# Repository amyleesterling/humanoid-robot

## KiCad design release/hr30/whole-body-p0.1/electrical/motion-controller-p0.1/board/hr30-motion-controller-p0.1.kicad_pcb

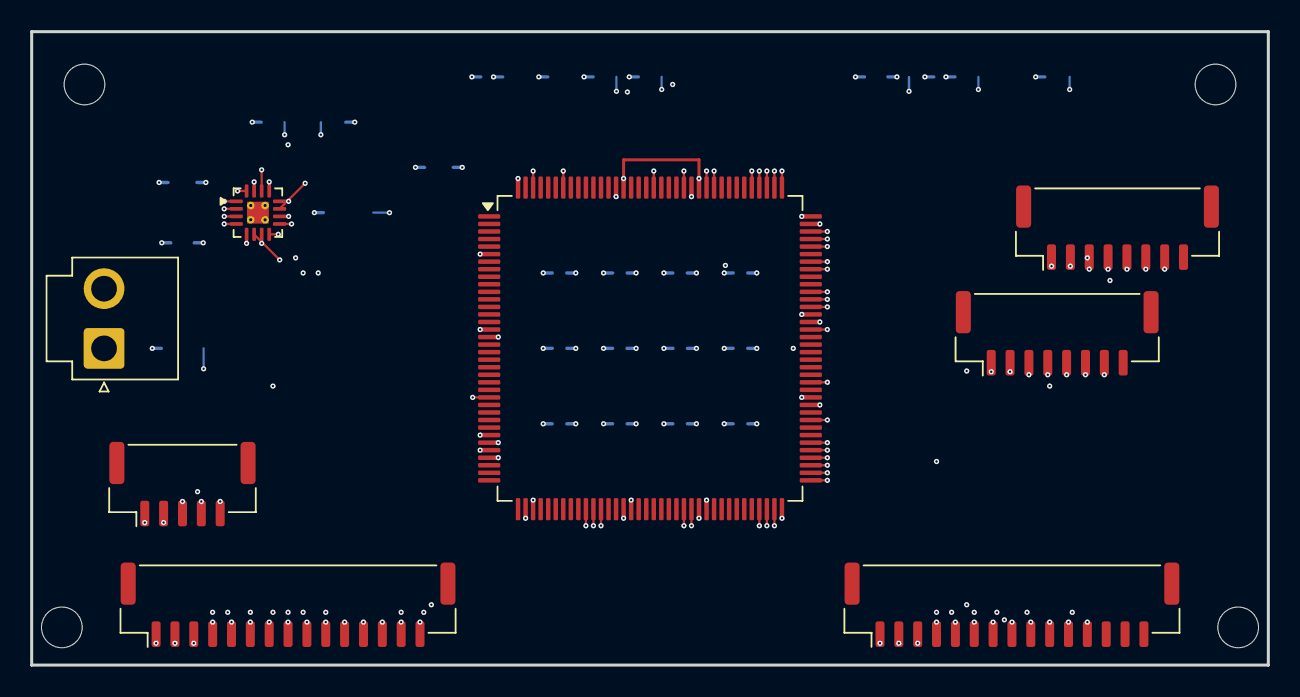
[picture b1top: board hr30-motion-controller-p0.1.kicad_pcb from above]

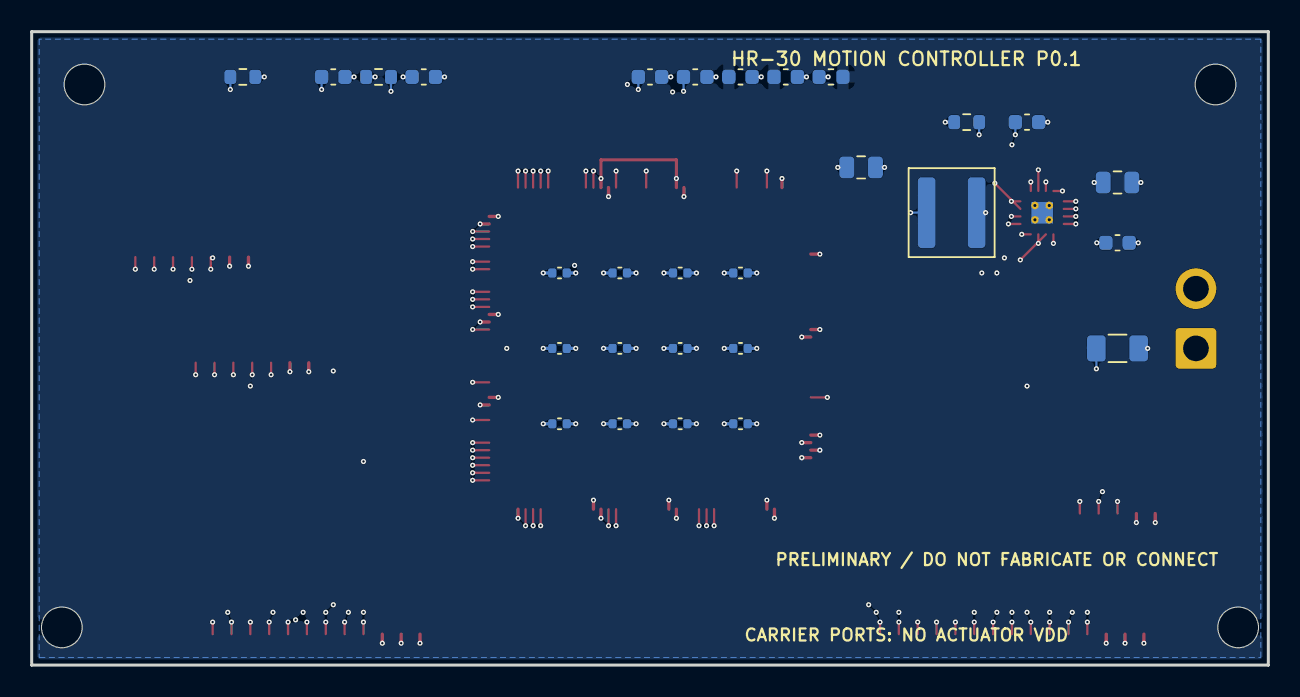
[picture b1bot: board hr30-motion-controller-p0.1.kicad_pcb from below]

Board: 6 copper layers, 82.0 x 42.0 mm, 40 parts (28 on the bottom side), 45 nets.

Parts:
C1, C2, C3, C4, C5, C6, C7, C8, C9, C10, C11, C12: 100 nF MCU supply bypass; C_0402_1005Metric
CANA1: 1 uF analog bypass; C_0603_1608Metric
CANA2: 100 nF analog bypass; C_0603_1608Metric
CBULK1: 4.7 uF MCU bulk; C_0603_1608Metric
CIN1: 10 uF 10 V X7R input; C_0805_2012Metric
CIN2: 100 nF 50 V X7R AVIN; C_0603_1608Metric
CNRST: 100 nF NRST filter; C_0603_1608Metric
COUT1: 22 uF 6.3 V X5R output; C_0805_2012Metric
CSS1: 3.3 nF soft-start; C_0603_1608Metric
CVC1: 2.2 uF VCAP1; C_0603_1608Metric
CVC2: 2.2 uF VCAP2; C_0603_1608Metric
F1: resettable input protection - selection required; Fuse_1206_3216Metric
FB1: analog-rail ferrite; L_0603_1608Metric
J1: Protected auxiliary 5 V input; JST_VH_B2P-VH-B_1x02_P3.96mm_Vertical
JACT1: structured action SPI boundary; JST_GH_BM08B-GHS-TBT_1x08-1MP_P1.25mm_Vertical
JCA1: Carrier A logic-only interface; JST_GH_BM15B-GHS-TBT_1x15-1MP_P1.25mm_Vertical
JCB1: Carrier B logic-only interface; JST_GH_BM15B-GHS-TBT_1x15-1MP_P1.25mm_Vertical
JDBG1: SWD programming/debug; JST_GH_BM05B-GHS-TBT_1x05-1MP_P1.25mm_Vertical
JIO1: deterministic status / inhibit I/O; JST_GH_BM08B-GHS-TBT_1x08-1MP_P1.25mm_Vertical
L1: 2.2 uH power inductor; L_Coilcraft_XAL5030-XXX
MHM1, MHM2, MHM3, MHM4: M2.5 BOARD-ONLY; TRAY STACK VALIDATION OPEN; MountingHole_2.7mm_M2.5
RBOOT: 100 k BOOT0 pull-down; R_0603_1608Metric
RNRST: 10 k NRST pull-up; R_0603_1608Metric
RPG1: 100 k power-good pull-up; R_0603_1608Metric
U1: STM32H743ZIT6 deterministic motion controller; LQFP-144_20x20mm_P0.5mm
U2: TPS62132 3.3 V / 3 A buck; VQFN-16-1EP_3x3mm_P0.5mm_EP1.45x1.45mm_ThermalVias

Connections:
ACTION_READY: JACT1.7, U1.126
ACTION_SPI_CS: JACT1.3, U1.73
ACTION_SPI_MISO: JACT1.5, U1.75
ACTION_SPI_MOSI: JACT1.6, U1.76
ACTION_SPI_SCK: JACT1.4, U1.74
AUX_5V_SAFE: F1.1, J1.2
BUCK_PG: RPG1.2, U2.4
BUCK_SS: CSS1.1, U2.9
BUCK_SW: L1.1, U2.1, U2.2, U2.3
CTRL_3V3: C1.1, C2.1, C3.1, C4.1, C5.1, C6.1, C7.1, C8.1, C9.1, C10.1, C11.1, C12.1, CBULK1.1, COUT1.1, FB1.1, JACT1.2, JCA1.3, JCB1.3, JDBG1.2, JIO1.2, L1.2, RNRST.1, RPG1.1, U1.6, U1.17, U1.30, U1.39, U1.52, U1.62, U1.72, U1.84, U1.95, U1.108, U1.121, U1.131, U1.144, U2.14
CTRL_3V3_ANALOG: CANA1.1, CANA2.1, FB1.2, U1.32, U1.33
CTRL_5V: CIN1.1, CIN2.1, F1.2, JCA1.2, JCB1.2, U2.10, U2.11, U2.12, U2.13
CTRL_GND: C1.2, C2.2, C3.2, C4.2, C5.2, C6.2, C7.2, C8.2, C9.2, C10.2, C11.2, C12.2, CANA1.2, CANA2.2, CBULK1.2, CIN1.2, CIN2.2, CNRST.2, COUT1.2, CSS1.2, CVC1.2, CVC2.2, J1.1, JACT1.1, JCA1.1, JCB1.1, JDBG1.1, JIO1.1, RBOOT.2, U1.16, U1.31, U1.38, U1.51, U1.61, U1.83, U1.94, U1.107, U1.120, U1.130, U2.5, U2.6, U2.7, U2.8, U2.15, U2.16, U2.17
MCU_BOOT0: RBOOT.1, U1.138
MCU_NRST: CNRST.1, JDBG1.5, RNRST.2, U1.25
MOTION_FAULT_DIAGNOSTIC: JIO1.7, U1.70
MOTION_WD_HEARTBEAT: JIO1.5, U1.48
PRECHARGE_REQUEST: JIO1.6, U1.69
PRECHARGE_STATUS: JIO1.4, U1.47
SAFETY_PERMIT_HARDWIRED: JIO1.3, U1.46
SWCLK: JDBG1.4, U1.109
SWDIO: JDBG1.3, U1.105
UART_RS-LARM_DIR: JCA1.12, U1.81
UART_RS-LARM_RX: JCA1.11, U1.78
UART_RS-LARM_TX: JCA1.10, U1.77
UART_RS-LLEG_DIR: JCA1.6, U1.104
UART_RS-LLEG_RX: JCA1.5, U1.102
UART_RS-LLEG_TX: JCA1.4, U1.101
UART_RS-RARM_DIR: JCA1.15, U1.93
UART_RS-RARM_RX: JCA1.14, U1.97
UART_RS-RARM_TX: JCA1.13, U1.96
UART_RS-RLEG_DIR: JCA1.9, U1.118
UART_RS-RLEG_RX: JCA1.8, U1.122
UART_RS-RLEG_TX: JCA1.7, U1.119
UART_RS-WAIST_DIR: JCB1.6, U1.110
UART_RS-WAIST_RX: JCB1.5, U1.112
UART_RS-WAIST_TX: JCB1.4, U1.111
UART_TTL-HEAD_DIR: JCB1.12, U1.86
UART_TTL-HEAD_TX: JCB1.11, U1.142
UART_TTL-LDIST_DIR: JCB1.8, U1.98
UART_TTL-LDIST_TX: JCB1.7, U1.113
UART_TTL-RDIST_DIR: JCB1.10, U1.60
UART_TTL-RDIST_TX: JCB1.9, U1.59
VCAP1: CVC1.1, U1.71
VCAP2: CVC2.1, U1.106

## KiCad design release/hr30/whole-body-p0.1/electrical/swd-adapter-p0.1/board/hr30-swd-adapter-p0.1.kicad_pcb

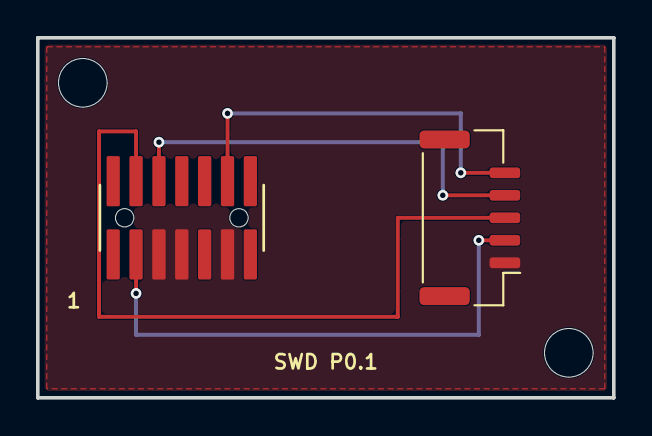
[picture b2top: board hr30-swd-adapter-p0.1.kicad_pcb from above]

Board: 2 copper layers, 32.0 x 20.0 mm, 4 parts (0 on the bottom side), 5 nets.

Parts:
H1, H2: M2.5 FIXTURE HOLE - MECHANICAL VALIDATION OPEN; MountingHole_2.7mm_M2.5
J1: FTSH-107-01-L-DV-K-A
J2: BM05B-GHS-TBT; JST_GH_BM05B-GHS-TBT_1x05-1MP_P1.25mm_Vertical

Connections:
CTRL_3V3: J1.3, J2.2
CTRL_GND: J1.5, J1.7, J1.11, J2.1
MCU_NRST: J1.12, J2.5
SWCLK: J1.6, J2.4
SWDIO: J1.4, J2.3

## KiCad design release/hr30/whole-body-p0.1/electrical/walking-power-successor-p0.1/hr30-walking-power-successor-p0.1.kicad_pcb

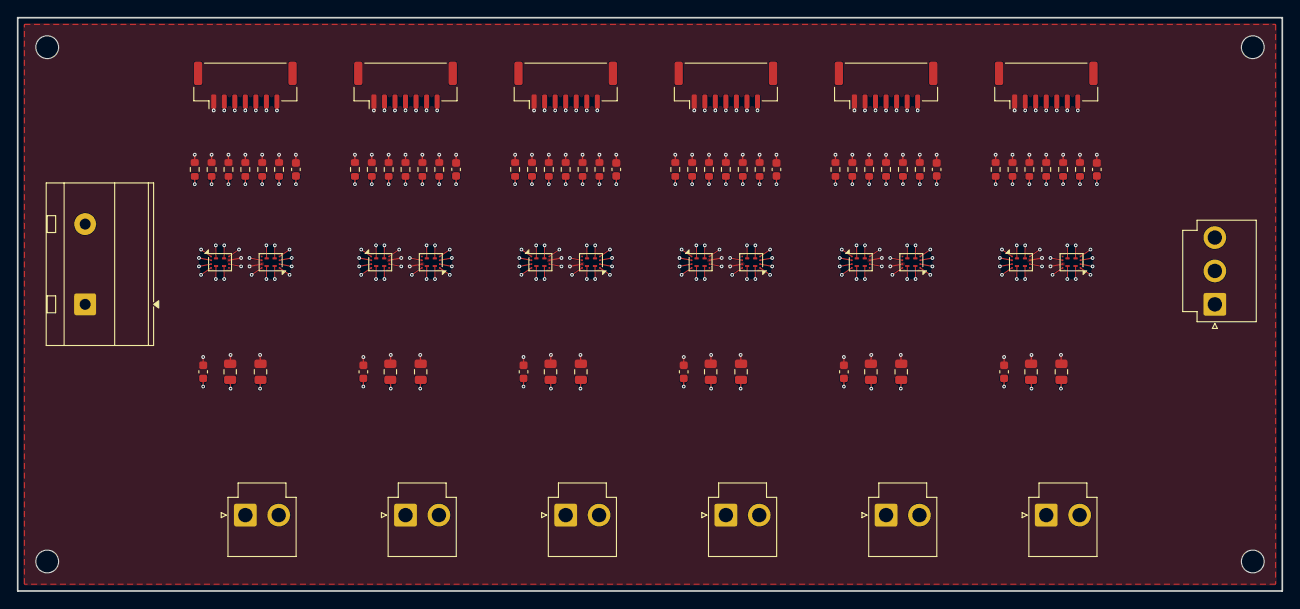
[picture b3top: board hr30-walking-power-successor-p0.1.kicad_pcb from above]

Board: 10 copper layers, 150.0 x 68.0 mm, 90 parts (0 on the bottom side), 74 nets.

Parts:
C1F, C2F, C3F, C4F, C5F, C6F: DVDT FORWARD - SELECTION REQUIRED; C_0603_1608Metric
C1I, C2I, C3I, C4I, C5I, C6I: INPUT BYPASS - SELECTION REQUIRED; C_0805_2012Metric
C1O, C2O, C3O, C4O, C5O, C6O: AXIS BYPASS - SELECTION REQUIRED; C_0805_2012Metric
C1R, C2R, C3R, C4R, C5R, C6R: DVDT REVERSE - SELECTION REQUIRED; C_0603_1608Metric
J1: CONTROLLED BUS-FEED INPUT; TerminalBlock_MetzConnect_Type703_RT10N02HGLU_1x02_P9.52mm_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
J1C: CHANNEL 1 CONTROL/MONITOR; JST_GH_BM07B-GHS-TBT_1x07-1MP_P1.25mm_Vertical
J1O: CHANNEL 1 AXIS OUTPUT; JST_VH_B2P-VH_1x02_P3.96mm_Vertical
J2C: CHANNEL 2 CONTROL/MONITOR; JST_GH_BM07B-GHS-TBT_1x07-1MP_P1.25mm_Vertical
J2O: CHANNEL 2 AXIS OUTPUT; JST_VH_B2P-VH_1x02_P3.96mm_Vertical
J3C: CHANNEL 3 CONTROL/MONITOR; JST_GH_BM07B-GHS-TBT_1x07-1MP_P1.25mm_Vertical
J3O: CHANNEL 3 AXIS OUTPUT; JST_VH_B2P-VH_1x02_P3.96mm_Vertical
J4C: CHANNEL 4 CONTROL/MONITOR; JST_GH_BM07B-GHS-TBT_1x07-1MP_P1.25mm_Vertical
J4O: CHANNEL 4 AXIS OUTPUT; JST_VH_B2P-VH_1x02_P3.96mm_Vertical
J5C: CHANNEL 5 CONTROL/MONITOR; JST_GH_BM07B-GHS-TBT_1x07-1MP_P1.25mm_Vertical
J5O: CHANNEL 5 AXIS OUTPUT; JST_VH_B2P-VH_1x02_P3.96mm_Vertical
J6C: CHANNEL 6 CONTROL/MONITOR; JST_GH_BM07B-GHS-TBT_1x07-1MP_P1.25mm_Vertical
J6O: CHANNEL 6 AXIS OUTPUT; JST_VH_B2P-VH_1x02_P3.96mm_Vertical
JBRK: EXTERNAL FEED BRAKE/DUMP INTERFACE; JST_VH_B3P-VH_1x03_P3.96mm_Vertical
MH1, MH2, MH3, MH4: M2.5 BOARD-ONLY; MountingHole_2.7mm_M2.5
R1B, R2B, R3B, R4B, R5B, R6B: 10k RCBCTRL pulldown; R_0603_1608Metric
R1E, R2E, R3E, R4E, R5E, R6E: 100k EN pulldown; R_0603_1608Metric
R1F, R2F, R3F, R4F, R5F, R6F: RILM FORWARD - SELECTION REQUIRED; R_0603_1608Metric
R1OF, R2OF, R3OF, R4OF, R5OF, R6OF: 0R OVLO FORWARD PULLDOWN CANDIDATE; R_0603_1608Metric
R1OR, R2OR, R3OR, R4OR, R5OR, R6OR: 0R OVLO REVERSE PULLDOWN CANDIDATE; R_0603_1608Metric
R1R, R2R, R3R, R4R, R5R, R6R: RILM REVERSE - SELECTION REQUIRED; R_0603_1608Metric
U1F, U2F, U3F, U4F, U5F, U6F: TPS259482L FORWARD OCP; TI_YWP0012A_PowerWCSP_2.441x1.728mm
U1R, U2R, U3R, U4R, U5R, U6R: TPS259482L REVERSE OCP; TI_YWP0012A_PowerWCSP_2.441x1.728mm

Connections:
BRANCH_1_VPOS: C1O.1, J1O.2, U1R.5, U1R.12
BRANCH_2_VPOS: C2O.1, J2O.2, U2R.5, U2R.12
BRANCH_3_VPOS: C3O.1, J3O.2, U3R.5, U3R.12
BRANCH_4_VPOS: C4O.1, J4O.2, U4R.5, U4R.12
BRANCH_5_VPOS: C5O.1, J5O.2, U5R.5, U5R.12
BRANCH_6_VPOS: C6O.1, J6O.2, U6R.5, U6R.12
CH1_DVDT_F: C1F.1, U1F.7
CH1_DVDT_R: C1R.1, U1R.7
CH1_EN: J1C.2, R1E.1, U1F.1, U1R.1
CH1_ILM_F: J1C.5, R1F.1, U1F.9
CH1_ILM_R: J1C.6, R1R.1, U1R.9
CH1_MID: U1F.6, U1F.11, U1R.6, U1R.11
CH1_OV_F: R1OF.1, U1F.2
CH1_OV_R: R1OR.1, U1R.2
CH1_PG_F: J1C.3, U1F.3
CH1_PG_R: J1C.4, U1R.3
CH1_RCBCTRL: J1C.7, R1B.1, U1F.4, U1R.4
CH2_DVDT_F: C2F.1, U2F.7
CH2_DVDT_R: C2R.1, U2R.7
CH2_EN: J2C.2, R2E.1, U2F.1, U2R.1
CH2_ILM_F: J2C.5, R2F.1, U2F.9
CH2_ILM_R: J2C.6, R2R.1, U2R.9
CH2_MID: U2F.6, U2F.11, U2R.6, U2R.11
CH2_OV_F: R2OF.1, U2F.2
CH2_OV_R: R2OR.1, U2R.2
CH2_PG_F: J2C.3, U2F.3
CH2_PG_R: J2C.4, U2R.3
CH2_RCBCTRL: J2C.7, R2B.1, U2F.4, U2R.4
CH3_DVDT_F: C3F.1, U3F.7
CH3_DVDT_R: C3R.1, U3R.7
CH3_EN: J3C.2, R3E.1, U3F.1, U3R.1
CH3_ILM_F: J3C.5, R3F.1, U3F.9
CH3_ILM_R: J3C.6, R3R.1, U3R.9
CH3_MID: U3F.6, U3F.11, U3R.6, U3R.11
CH3_OV_F: R3OF.1, U3F.2
CH3_OV_R: R3OR.1, U3R.2
CH3_PG_F: J3C.3, U3F.3
CH3_PG_R: J3C.4, U3R.3
CH3_RCBCTRL: J3C.7, R3B.1, U3F.4, U3R.4
CH4_DVDT_F: C4F.1, U4F.7
CH4_DVDT_R: C4R.1, U4R.7
CH4_EN: J4C.2, R4E.1, U4F.1, U4R.1
CH4_ILM_F: J4C.5, R4F.1, U4F.9
CH4_ILM_R: J4C.6, R4R.1, U4R.9
CH4_MID: U4F.6, U4F.11, U4R.6, U4R.11
CH4_OV_F: R4OF.1, U4F.2
CH4_OV_R: R4OR.1, U4R.2
CH4_PG_F: J4C.3, U4F.3
CH4_PG_R: J4C.4, U4R.3
CH4_RCBCTRL: J4C.7, R4B.1, U4F.4, U4R.4
CH5_DVDT_F: C5F.1, U5F.7
CH5_DVDT_R: C5R.1, U5R.7
CH5_EN: J5C.2, R5E.1, U5F.1, U5R.1
CH5_ILM_F: J5C.5, R5F.1, U5F.9
CH5_ILM_R: J5C.6, R5R.1, U5R.9
CH5_MID: U5F.6, U5F.11, U5R.6, U5R.11
CH5_OV_F: R5OF.1, U5F.2
CH5_OV_R: R5OR.1, U5R.2
CH5_PG_F: J5C.3, U5F.3
CH5_PG_R: J5C.4, U5R.3
CH5_RCBCTRL: J5C.7, R5B.1, U5F.4, U5R.4
CH6_DVDT_F: C6F.1, U6F.7
CH6_DVDT_R: C6R.1, U6R.7
CH6_EN: J6C.2, R6E.1, U6F.1, U6R.1
CH6_ILM_F: J6C.5, R6F.1, U6F.9
CH6_ILM_R: J6C.6, R6R.1, U6R.9
CH6_MID: U6F.6, U6F.11, U6R.6, U6R.11
CH6_OV_F: R6OF.1, U6F.2
CH6_OV_R: R6OR.1, U6R.2
CH6_PG_F: J6C.3, U6F.3
CH6_PG_R: J6C.4, U6R.3
CH6_RCBCTRL: J6C.7, R6B.1, U6F.4, U6R.4
FEED_0V: C1F.2, C1I.2, C1O.2, C1R.2, C2F.2, C2I.2, C2O.2, C2R.2, C3F.2, C3I.2, C3O.2, C3R.2, C4F.2, C4I.2, C4O.2, C4R.2, C5F.2, C5I.2, C5O.2, C5R.2, C6F.2, C6I.2, C6O.2, C6R.2, J1.1, J1C.1, J1O.1, J2C.1, J2O.1, J3C.1, J3O.1, J4C.1, J4O.1, J5C.1, J5O.1, J6C.1, J6O.1, JBRK.1, R1B.2, R1E.2, R1F.2, R1OF.2, R1OR.2, R1R.2, R2B.2, R2E.2, R2F.2, R2OF.2, R2OR.2, R2R.2, R3B.2, R3E.2, R3F.2, R3OF.2, R3OR.2, R3R.2, R4B.2, R4E.2, R4F.2, R4OF.2, R4OR.2, R4R.2, R5B.2, R5E.2, R5F.2, R5OF.2, R5OR.2, R5R.2, R6B.2, R6E.2, R6F.2, R6OF.2, R6OR.2, R6R.2, U1F.8, U1R.8, U2F.8, U2R.8, U3F.8, U3R.8, U4F.8, U4R.8, U5F.8, U5R.8, U6F.8, U6R.8
FEED_VPOS: C1I.1, C2I.1, C3I.1, C4I.1, C5I.1, C6I.1, J1.2, JBRK.2, U1F.5, U1F.12, U2F.5, U2F.12, U3F.5, U3F.12, U4F.5, U4F.12, U5F.5, U5F.12, U6F.5, U6F.12
